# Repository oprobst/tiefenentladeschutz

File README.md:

# tiefenentladeschutz
Tiefenentladeschutz für Akkutank

Details siehe http://www.tief-dunkel-kalt.org/index.php/blog/33-wir-bauen-einen-akku-teil-2

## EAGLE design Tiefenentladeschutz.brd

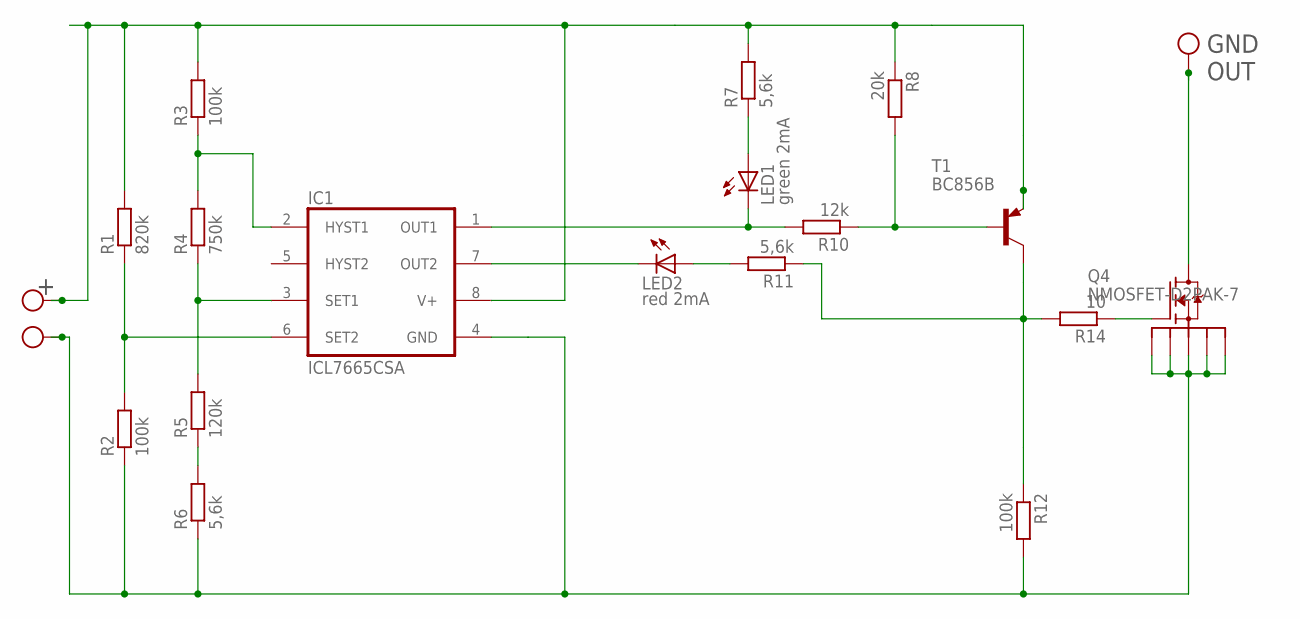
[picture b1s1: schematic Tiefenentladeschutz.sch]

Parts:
IC1: ICL7665CSA; SO08
LED1: green 2mA; LED_SML0603
LED2: red 2mA; LED_SML0603
Q4: NMOSFET-D2PAK-7; H2PAK-6
R1: 820k; R0603
R2: 100k; R0603
R3: 100k; M1206
R4: 750k; R0603
R5: 120k; R0603
R6, R7, R11: 5,6k; R0603
R8: 20k; R0603
R10: 12k; R0603
R12: 100k; R1206
R14: 10; R0603
T1: BC856B; SOT23-BEC
U$4: PIN2.54; PIN
U$6, U$7: PIN1.27; PIN-1.27

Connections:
GND: IC1.4 (GND), Q4.S1, Q4.S2, Q4.S3, Q4.S4, Q4.S5, R2.1, R6.1, R12.2, U$6.P$1
unnamed: Q4.D, U$7.P$1
unnamed: IC1.3 (SET1), R4.1, R5.2
unnamed: IC1.7 (OUT2), LED2.C
unnamed: IC1.6 (SET2), R1.1, R2.2
unnamed: LED2.A, R11.2
unnamed: LED1.A, R7.1
unnamed: R8.2, R10.1, T1.B
unnamed: Q4.G, R14.1
unnamed: IC1.2 (HYST1), R3.1, R4.2
unnamed: IC1.1 (OUT1), LED1.C, R10.2
unnamed: R11.1, R12.1, R14.2, T1.C
unnamed: R5.1, R6.2
V+: IC1.8 (V+), R1.2, R3.2, R7.2, R8.1, T1.E, U$4.P$1

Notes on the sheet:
GND OUT

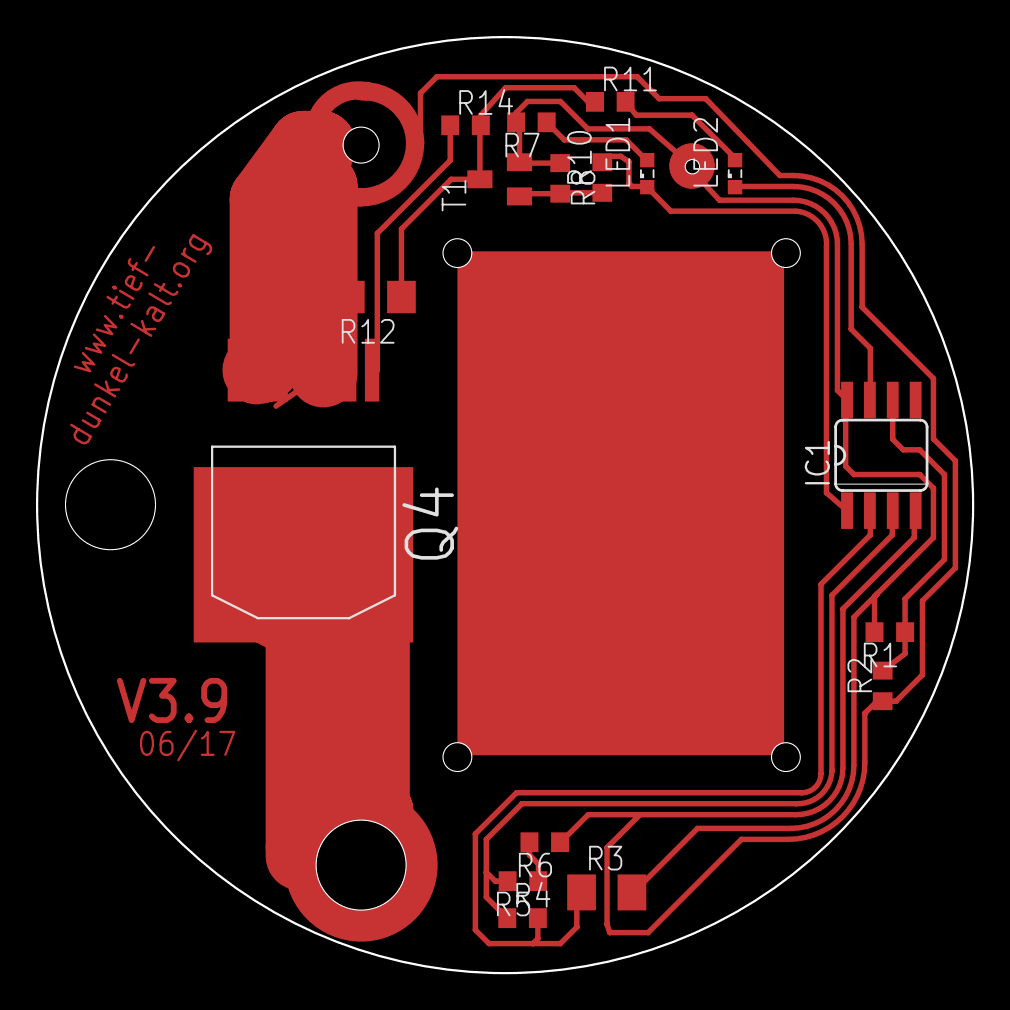
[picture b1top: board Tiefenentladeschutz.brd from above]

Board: 2 copper layers, 52.0 x 52.0 mm, 22 parts (0 on the bottom side), 14 nets.

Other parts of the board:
U$1, U$5: PIN-GENERIC; LEER

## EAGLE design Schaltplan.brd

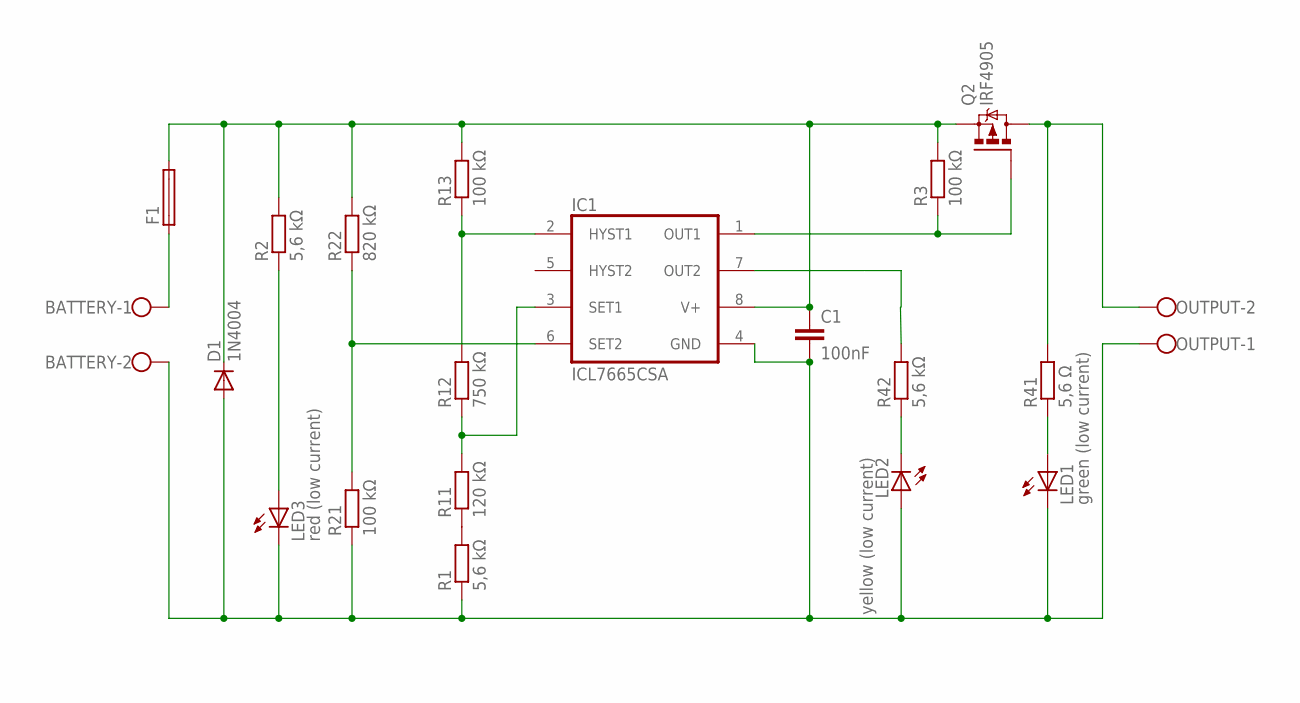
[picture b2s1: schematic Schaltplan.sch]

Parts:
BATTERY: W237-102
C1: 100nF; C0603
D1: 1N4004; DO41-10
F1: GSH15
IC1: ICL7665CSA; SO08
LED1: green (low current); SML0603
LED2: yellow (low current); KA-3528ASYC
LED3: red (low current); KA-3528ASYC
OUTPUT: W237-102
Q2: IRF4905; TO220BH
R1, R2, R42: 5,6 kΩ; R1206
R3, R13, R21: 100 kΩ; R1206
R11: 120 kΩ; R1206
R12: 750 kΩ; R1206
R22: 820 kΩ; R1206
R41: 5,6 Ω; R1206

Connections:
GND: BATTERY.2, C1.2, D1.A, IC1.4 (GND), LED1.C, LED2.A, LED3.C, OUTPUT.1, R1.1, R21.1
unnamed: LED3.A, R2.1
unnamed: IC1.6 (SET2), R21.2, R22.1
unnamed: IC1.2 (HYST1), R12.2, R13.1
unnamed: OUTPUT.2, Q2.D, R41.2
unnamed: IC1.3 (SET1), R11.2, R12.1
unnamed: IC1.1 (OUT1), Q2.G, R3.1
unnamed: LED1.A, R41.1
unnamed: LED2.C, R42.1
unnamed: R1.2, R11.1
unnamed: BATTERY.1, F1.1
POWER: C1.1, D1.C, F1.2, IC1.8 (V+), Q2.S, R2.2, R3.2, R13.2, R22.2

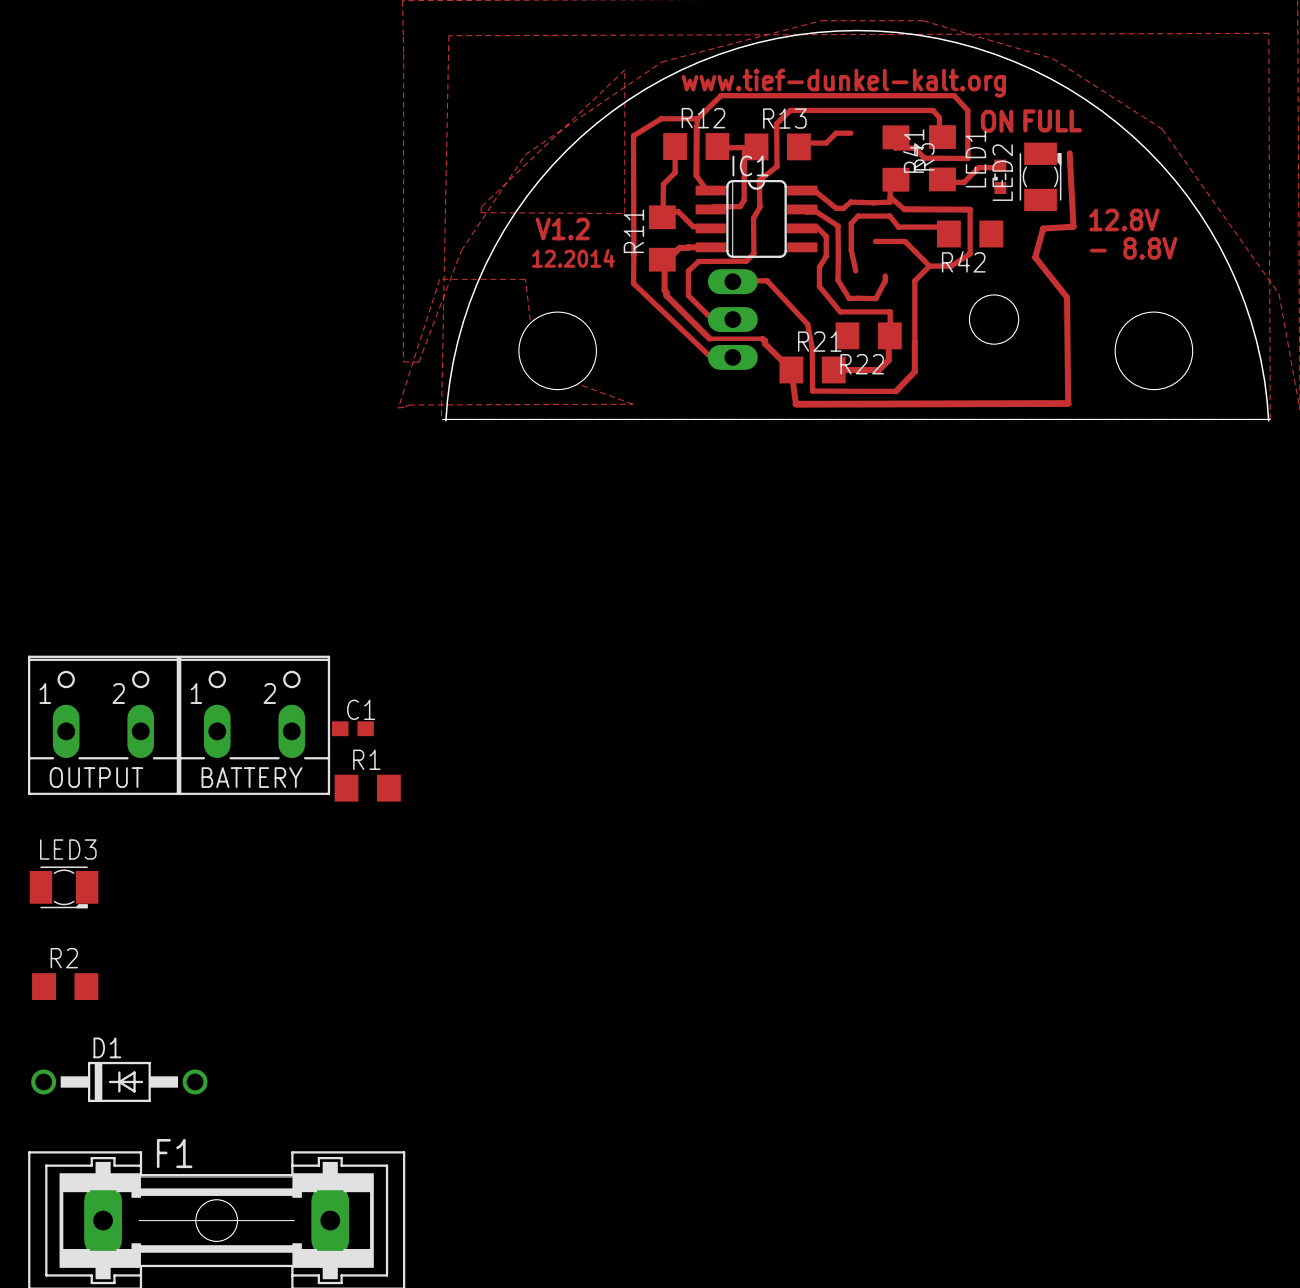
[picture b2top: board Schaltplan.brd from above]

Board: 2 copper layers, 55.5 x 26.2 mm, 21 parts (1 on the bottom side), 12 nets.

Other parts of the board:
U$1: PIN-GENERIC; LEER

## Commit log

2016-02-02 version 1.1
2016-02-02 v 1.2
2016-02-02 v 2.3
2016-02-02 v2.4
2016-02-02 renamed files
2016-02-02 added Schaltplan-export.jpg
2016-04-25 Added Mosfet Gate Resistors
2016-04-25 Updated image export of schematic
2017-02-18 Ohne LED added, replaced P-mosfet by bipolar
2017-02-18 R12 to 100kOhm
2017-02-18 R12 to 100 kOhm
2017-06-03 Smaller Resistors, less transistors, smaller pcb
2017-06-11 Some wiring adjustments
2017-07-08 Breitere Leiterbahnen und Gehäuse Modell
